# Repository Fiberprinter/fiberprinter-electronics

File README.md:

<div align="center">
<h1 align="center">

<br>Fiberelectronics
</h1>
<h3>Control every pulse, master every micron</h3>

</div>

</h1>

# Fiberprinter Electronics

Dieses Repository enthält die Elektronikentwicklung für den faserverlegenden 3D-Drucker, der im Rahmen einer Diplomarbeit an der HTBLA Kaindorf entwickelt wird. Die Elektronik umfasst sowohl die Steuerung der Druckkopffunktionen als auch die Anbindung an das Hauptsystem mittels eines Raspberry Pi mit **Klipper-Firmware**.

## 📌 Projektübersicht

Das Ziel dieses Projekts ist die Entwicklung einer modularen und effizienten Steuerung für den Druckkopf, die über eine eigenentwickelte Platine mit einem **ATmega328** realisiert wird. Diese übernimmt spezifische Aufgaben, die über das Hauptsystem des Druckers nicht direkt gesteuert werden.

## ⚙️ Hauptkomponenten

### 1️⃣ **Steuerungshardware**
- **Raspberry Pi** mit Klipper-Firmware zur übergeordneten Steuerung
- **Eigenes Mainboard mit ATmega328** zur Ansteuerung folgender Komponenten:
  - Lüfter
  - BL Touch (Autoleveling-Sensor)
  - Servo
  - Schrittmotor
  - Temperatursensoren
- **Breakout-Board für den ATmega2560**, das Test- und Messpunkte sowie einen Bootloader enthält
- **FT232RL** als USB-to-Serial-Adapter für die Kommunikation mit dem ATmega2560
- **Reset-Button** zur einfachen Rücksetzung des Systems

### 2️⃣ **Firmware & Kommunikation**
- Der **ATmega328** wird von der Klipper-Firmware auf dem Raspberry Pi über USB angesprochen
- Kommunikation erfolgt über **serielles Protokoll**
- Entwicklung einer **angepassten Firmware für den ATmega328**, um die spezifischen Druckkopf-Funktionen auszuführen

### 3️⃣ **Software**
- Python-Skript zur **Integration der Steuerung in Klipper**
- Implementierung eines Protokolls zur **Steuerung der Hardware aus Klipper heraus**
- Zusammenarbeit mit der **Slicing-Software**, um die gezielte Faserverlegung zu ermöglichen

## 🛠️ Entwicklungsteam

- **Jan Traußnigg** – Elektronikdesign & Firmware
- **Nico Hütter** – Konstruktion, Aufbau & Testung
- **Elias Gottsbacher** – Slicing-Software & Software-Integration

## 📜 Lizenz

Dieses Projekt steht unter der **MIT-Lizenz**. Weitere Details sind in der Datei `LICENSE` zu finden.

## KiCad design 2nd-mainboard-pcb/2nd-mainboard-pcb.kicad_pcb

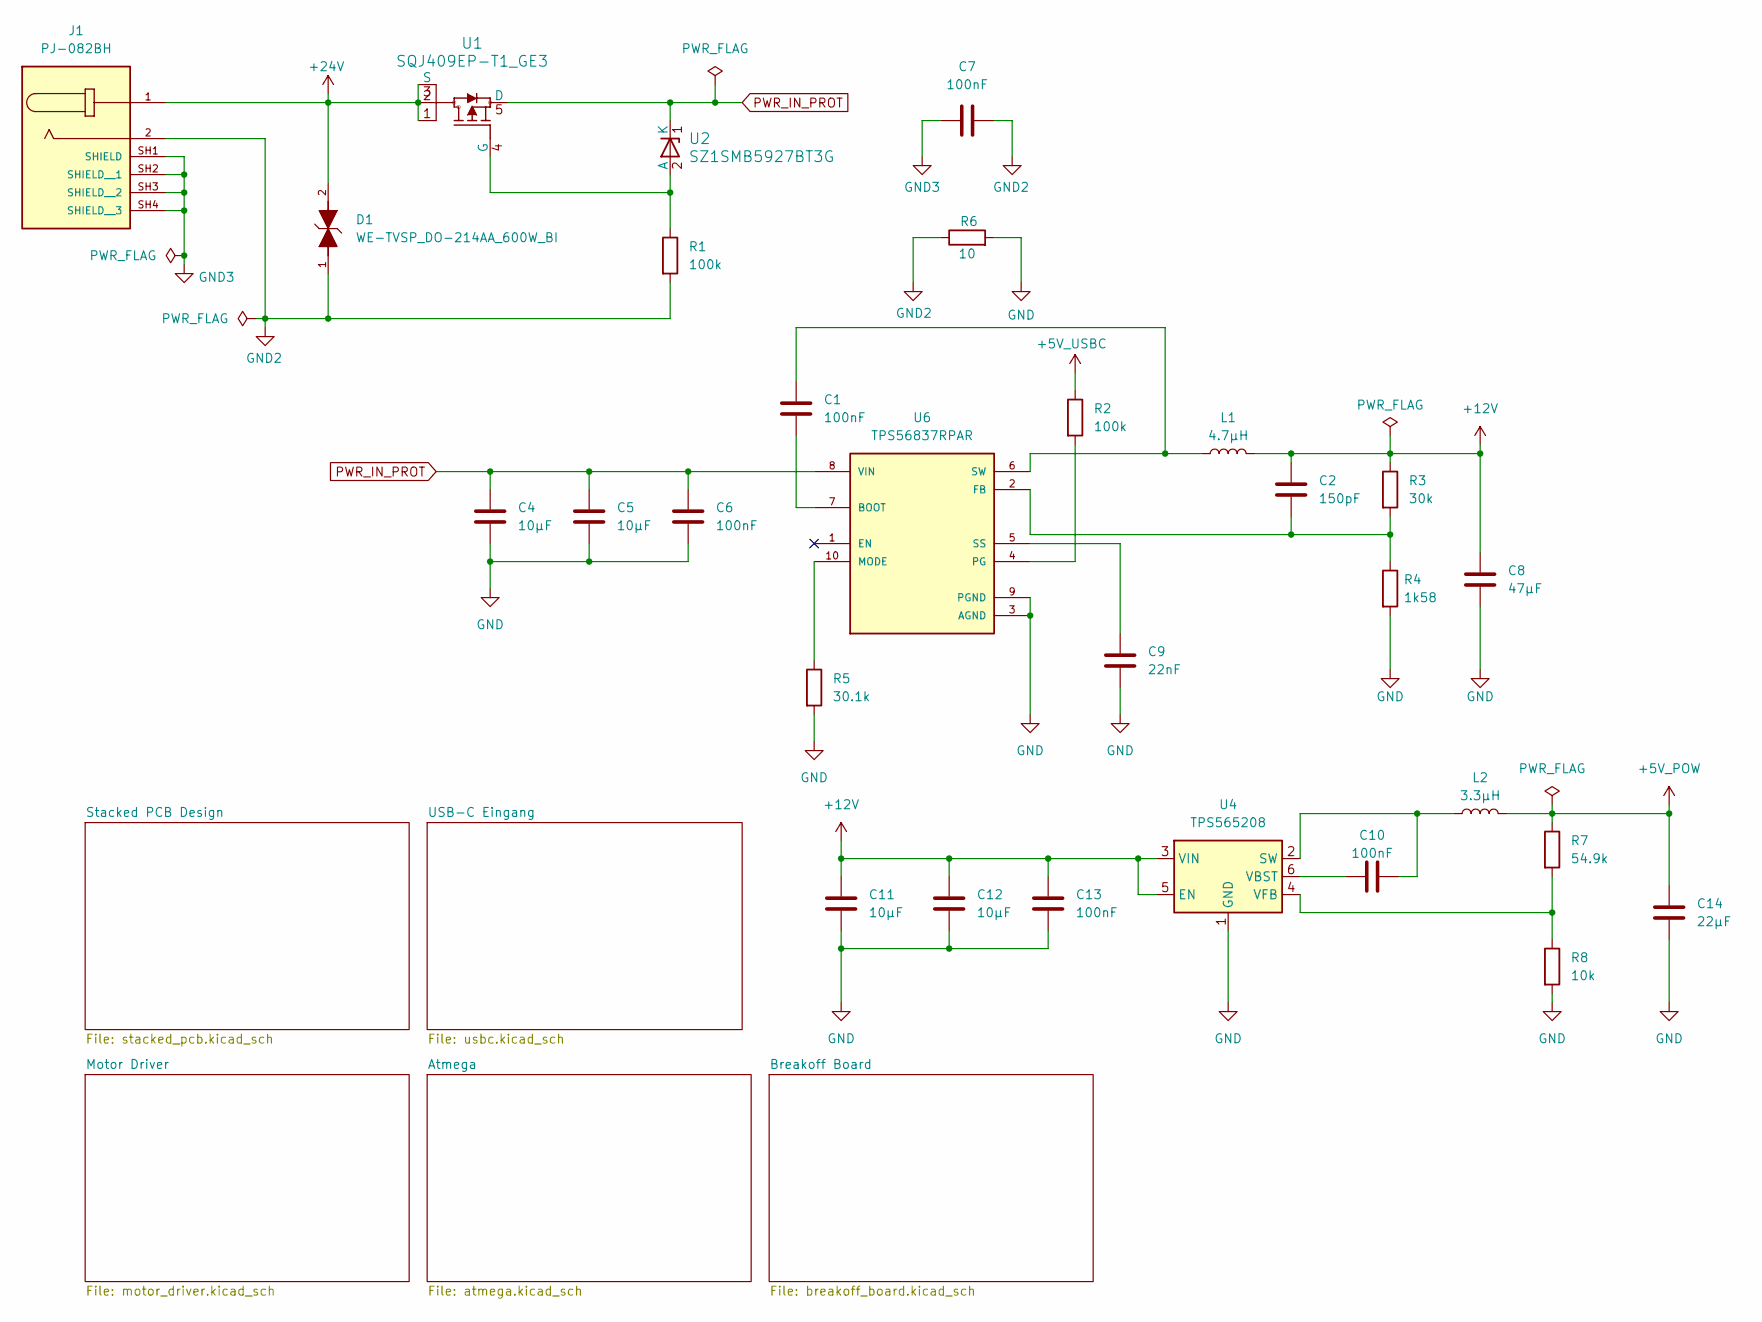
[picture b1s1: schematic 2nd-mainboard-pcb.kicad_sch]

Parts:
C1, C7, C10, C13: 100nF; C_0603_1608Metric_Pad1.08x0.95mm_HandSolder
C2: 150pF; C_0603_1608Metric_Pad1.08x0.95mm_HandSolder
C4, C5: 10µF; C_1210_3225Metric_Pad1.33x2.70mm_HandSolder
C6: 100nF; C_0805_2012Metric_Pad1.18x1.45mm_HandSolder
C8: 47µF; C_1812_4532Metric_Pad1.57x3.40mm_HandSolder
C9: 22nF; C_0603_1608Metric_Pad1.08x0.95mm_HandSolder
C11, C12: 10µF; C_0805_2012Metric_Pad1.18x1.45mm_HandSolder
C14: 22µF; C_1210_3225Metric_Pad1.33x2.70mm_HandSolder
D1: WE-TVSP_DO-214AA_600W_BI; 824521241
J1: PJ-082BH; CUI_PJ-082BH; PARTREV 1.04
L1: 4.7µH; SPM10040T_4R7M_HZ
L2: 3.3µH; IHLP2525CZER3R3M11
R1, R2: 100k; R_0603_1608Metric_Pad0.98x0.95mm_HandSolder
R3: 30k; R_0603_1608Metric_Pad0.98x0.95mm_HandSolder
R4: 1k58; R_0603_1608Metric_Pad0.98x0.95mm_HandSolder
R5: 30.1k; R_0603_1608Metric_Pad0.98x0.95mm_HandSolder
R6: 10; R_0603_1608Metric_Pad0.98x0.95mm_HandSolder
R7: 54.9k; R_0603_1608Metric_Pad0.98x0.95mm_HandSolder
R8: 10k; R_0603_1608Metric_Pad0.98x0.95mm_HandSolder
U1: SQJ409EP-T1_GE3; SQJ409EP_T1_GE3
U2: SZ1SMB5927BT3G
U4: TPS565208; SOT-23-6
U6: TPS56837RPAR; CONV_TPS56837RPAR; PARTREV A

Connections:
+5V_POW: C14.1, L2.2, R7.1; also elsewhere on the board
+12V: C2.1, C8.1, C11.1, C12.1, C13.1, L1.2, R3.1, U4.3 (VIN), U4.5 (EN); also elsewhere on the board
+24V: D1.2, J1.1, U1.1, U1.2, U1.3 (S)
AREF: R2.1; also elsewhere on the board
GND: C4.2, C5.2, C6.2, C8.2, C9.2, C11.2, C12.2, C13.2, C14.2, R4.2, R5.2, R6.2, R8.2, U4.1 (GND), U6.3 (AGND), U6.9 (PGND); also elsewhere on the board
GND2: C7.2, D1.1, J1.2, R1.2, R6.1
GND3: C7.1, J1.SH1 (SHIELD), J1.SH2 (SHIELD__1), J1.SH3 (SHIELD__2), J1.SH4 (SHIELD__3)
unnamed: R1.1, U1.4 (G), U2.2 (A)
unnamed: C10.2, L2.1, U4.2 (SW)
unnamed: C10.1, U4.6 (VBST)
unnamed: R7.2, R8.1, U4.4 (VFB)
unnamed: C1.1, U6.7 (BOOT)
unnamed: C2.2, R3.2, R4.1, U6.2 (FB)
unnamed: R5.1, U6.10 (MODE)
unnamed: R2.2, U6.4 (PG)
unnamed: C9.1, U6.5 (SS)
unnamed: C1.2, L1.1, U6.6 (SW)
PWR_IN_PROT: C4.1, C5.1, C6.1, U1.5 (D), U2.1 (K), U6.8 (VIN)

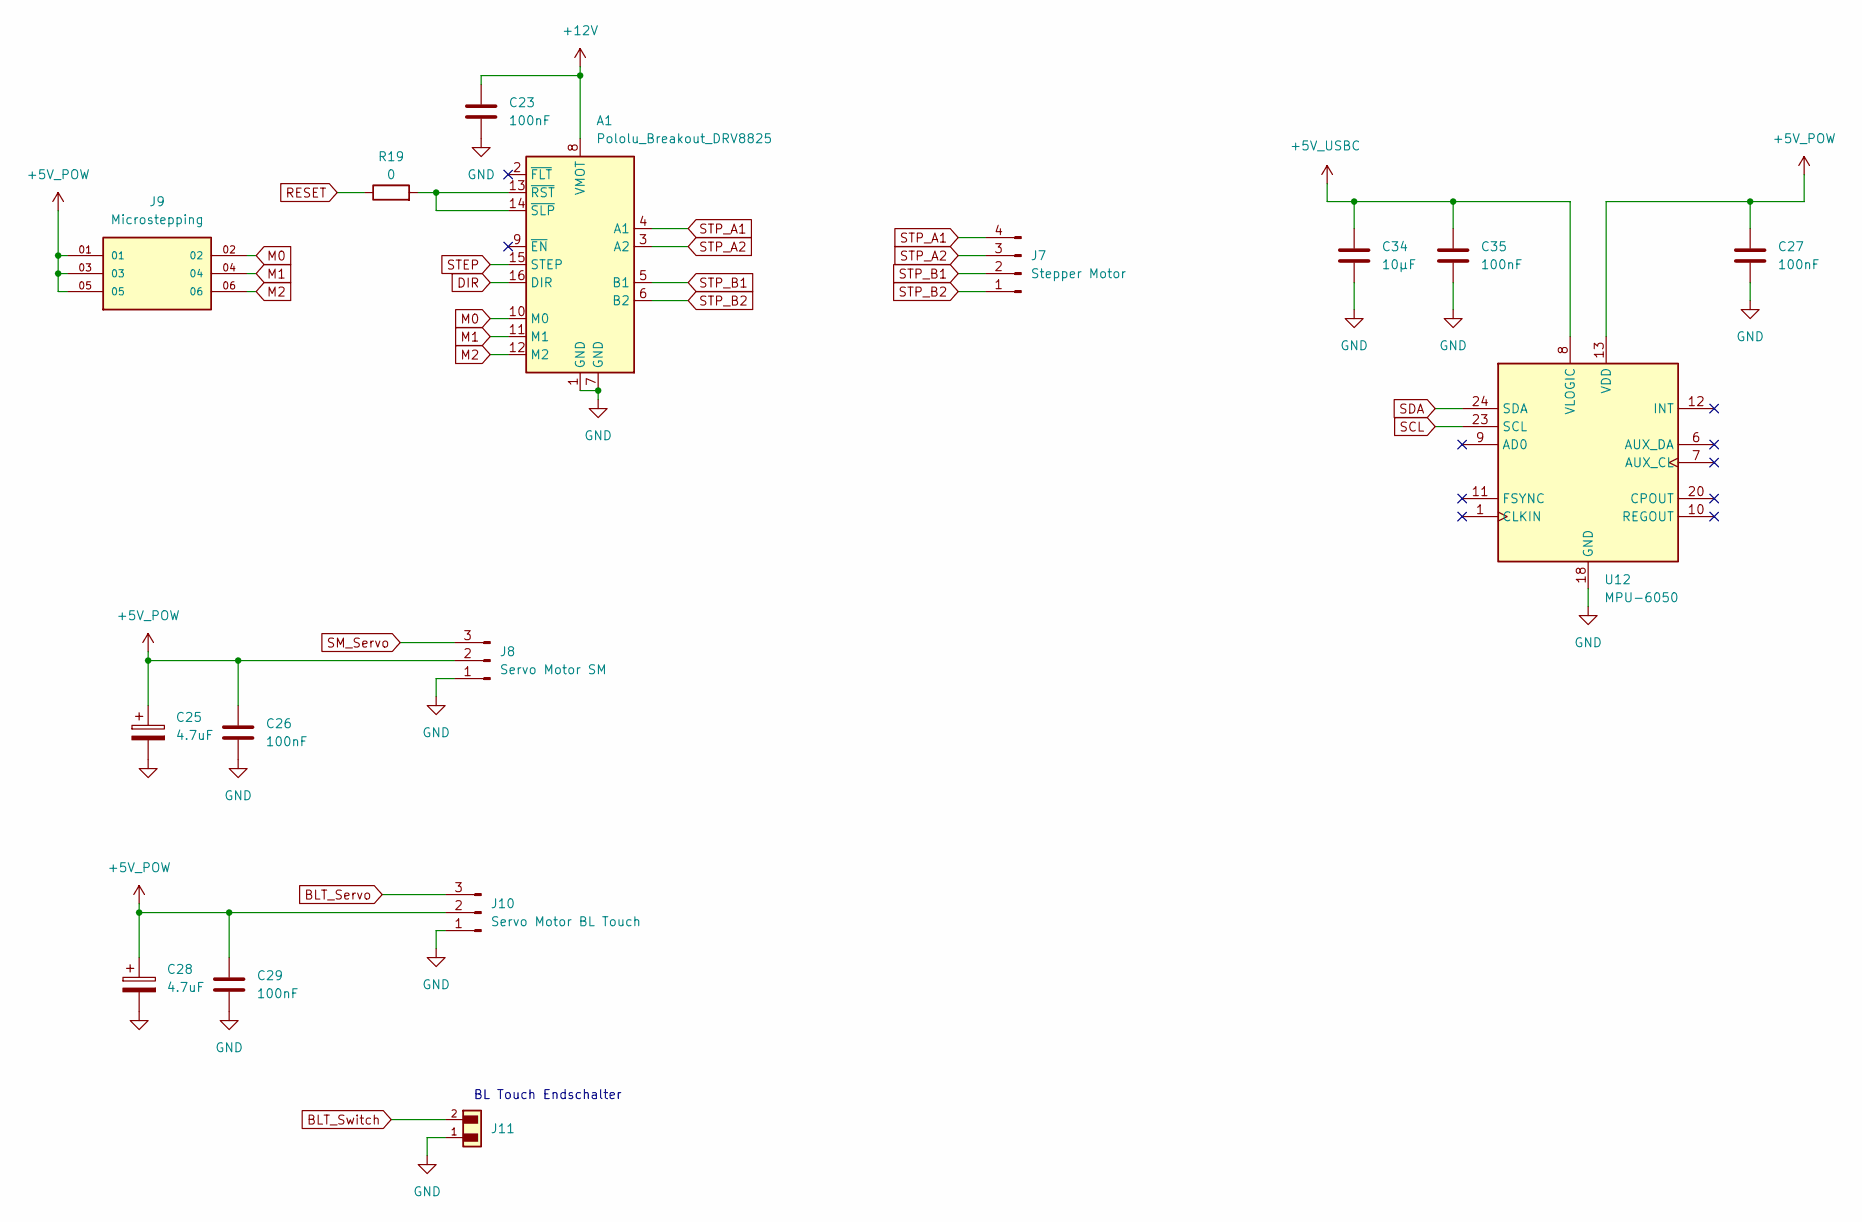
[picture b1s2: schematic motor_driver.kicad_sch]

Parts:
A1: Pololu_Breakout_DRV8825; drv8825
C23, C26, C27, C29, C35: 100nF; C_0603_1608Metric_Pad1.08x0.95mm_HandSolder
C25, C28: 4.7uF; C_0805_2012Metric_Pad1.18x1.45mm_HandSolder
C34: 10µF; C_0805_2012Metric_Pad1.18x1.45mm_HandSolder
J7: Stepper Motor; JST_S4B-XH-A-1
J8: Servo Motor SM; JST_XH_S3B-XH-A_1x03_P2.50mm_Horizontal
J9: Microstepping; FTSH-103-01-L-DH; PARTREV R
J10: Servo Motor BL Touch; JST_XH_S3B-XH-A_1x03_P2.50mm_Horizontal
J11: T3; 665102131822; PART-NUMBER 665102131822
R19: 0; R_0603_1608Metric_Pad0.98x0.95mm_HandSolder
U12: MPU-6050; InvenSense_QFN-24_4x4mm_P0.5mm

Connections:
+5V_POW: C25.1, C26.1, C27.1, C28.1, C29.1, J8.2, J9.01, J9.03, J9.05, J10.2, U12.13 (VDD); also elsewhere on the board
+12V: A1.8 (VMOT), C23.1; also elsewhere on the board
AREF: C34.1, C35.1, U12.8 (VLOGIC); also elsewhere on the board
BLT_Servo: J10.3; also elsewhere on the board
BLT_Switch: J11.2; also elsewhere on the board
DIR: A1.16 (DIR); also elsewhere on the board
GND: A1.1 (GND), A1.7 (GND), C23.2, C25.2, C26.2, C27.2, C28.2, C29.2, C34.2, C35.2, J8.1, J10.1, J11.1, U12.18 (GND); also elsewhere on the board
M0: A1.10 (M0), J9.02
M1: A1.11 (M1), J9.04
M2: A1.12 (M2), J9.06
MOSI: J8.3; also elsewhere on the board
unnamed: A1.13 (~RST), A1.14 (~SLP), R19.2
RESET: R19.1; also elsewhere on the board
SCL: U12.23 (SCL); also elsewhere on the board
SDA: U12.24 (SDA); also elsewhere on the board
STEP: A1.15 (STEP); also elsewhere on the board
STP_A1: A1.4 (A1), J7.4
STP_A2: A1.3 (A2), J7.3
STP_B1: A1.5 (B1), J7.2
STP_B2: A1.6 (B2), J7.1

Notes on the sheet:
BL Touch Endschalter

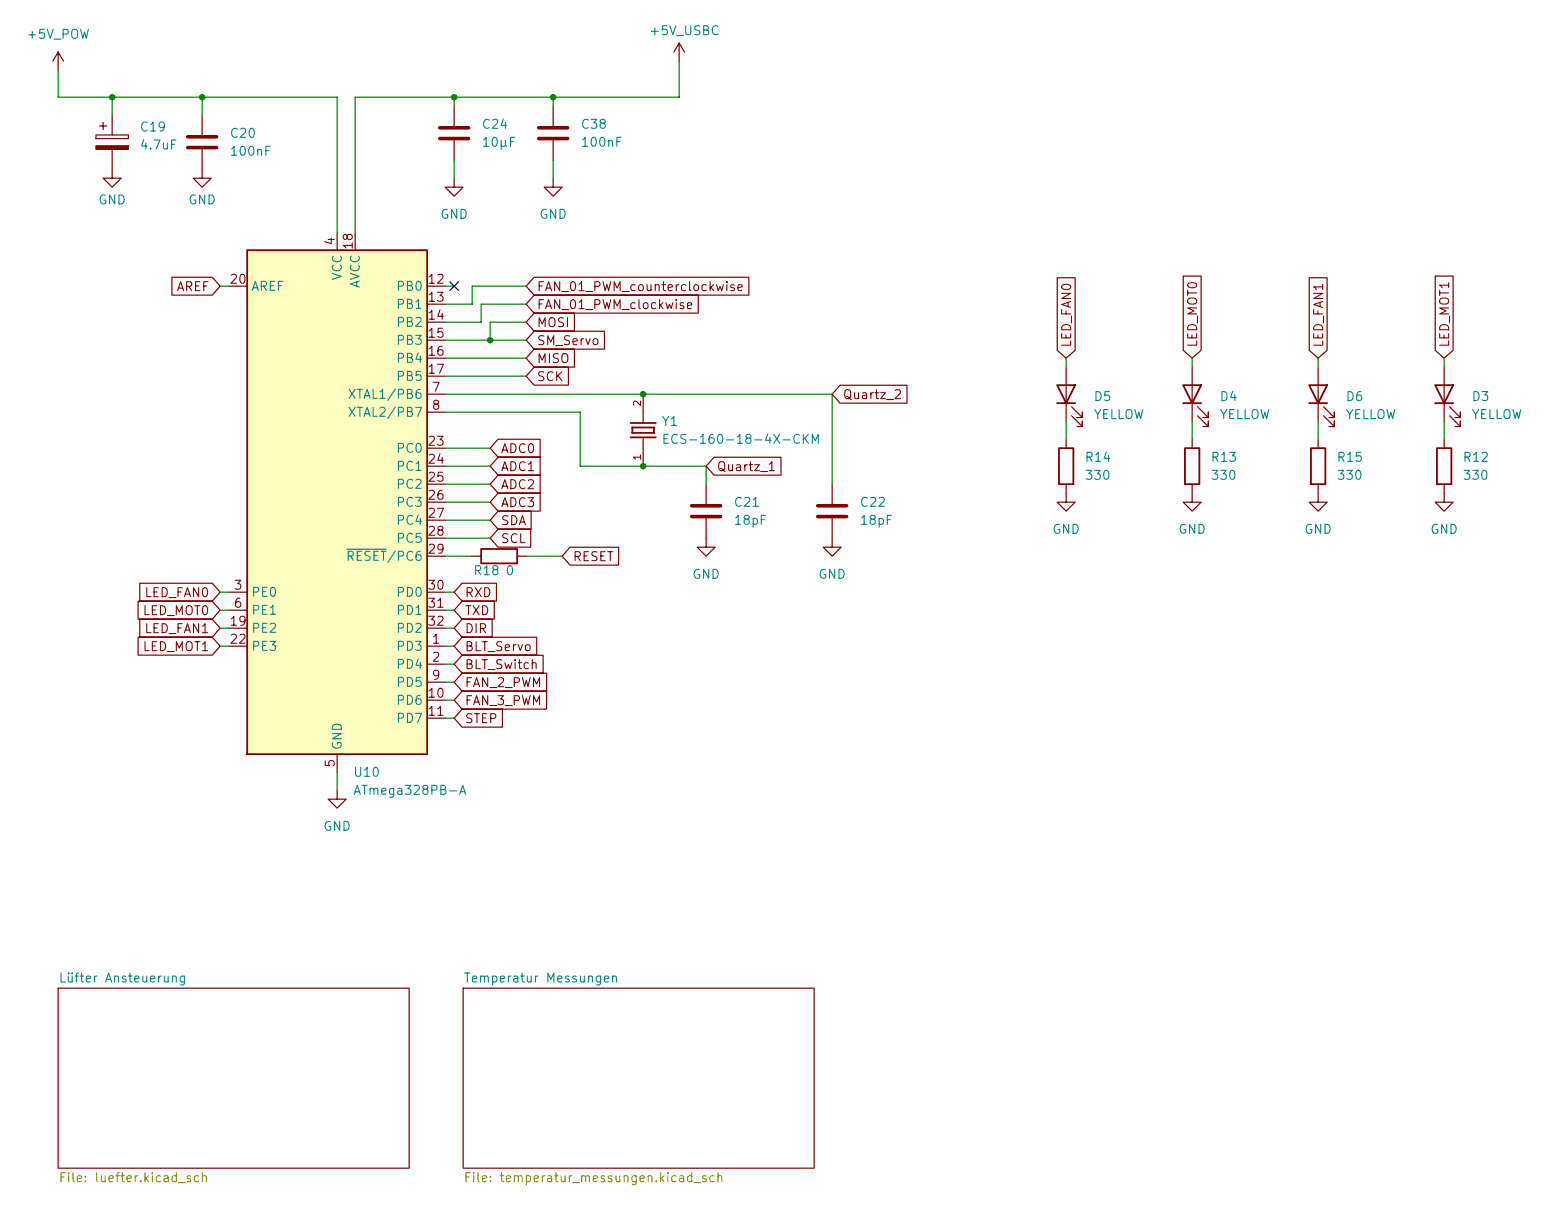
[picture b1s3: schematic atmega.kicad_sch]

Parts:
C19: 4.7uF; C_0805_2012Metric_Pad1.18x1.45mm_HandSolder
C20, C38: 100nF; C_0603_1608Metric_Pad1.08x0.95mm_HandSolder
C21, C22: 18pF; C_0603_1608Metric_Pad1.08x0.95mm_HandSolder
C24: 10µF; C_0805_2012Metric_Pad1.18x1.45mm_HandSolder
D3, D4, D5, D6: YELLOW; LED_0805_2012Metric
R12, R13, R14, R15: 330; R_0603_1608Metric_Pad0.98x0.95mm_HandSolder
R18: 0; R_0603_1608Metric_Pad0.98x0.95mm_HandSolder
U10: ATmega328PB-A; TQFP-32_7x7mm_P0.8mm
Y1: ECS-160-18-4X-CKM; XTAL_ECS-160-18-4X-CKM

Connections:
+5V_POW: C19.1, C20.1, U10.4 (VCC); also elsewhere on the board
ADC0: U10.23 (PC0); also elsewhere on the board
ADC1: U10.24 (PC1); also elsewhere on the board
ADC2: U10.25 (PC2); also elsewhere on the board
ADC3: U10.26 (PC3); also elsewhere on the board
AREF: C24.1, C38.1, U10.18 (AVCC), U10.20 (AREF); also elsewhere on the board
BLT_Servo: U10.1 (PD3); also elsewhere on the board
BLT_Switch: U10.2 (PD4); also elsewhere on the board
DIR: U10.32 (PD2); also elsewhere on the board
FAN_01_PWM_clockwise: U10.14 (PB2); also elsewhere on the board
FAN_01_PWM_counterclockwise: U10.13 (PB1); also elsewhere on the board
FAN_2_PWM: U10.9 (PD5); also elsewhere on the board
FAN_3_PWM: U10.10 (PD6); also elsewhere on the board
GND: C19.2, C20.2, C21.2, C22.2, C24.2, C38.2, R12.2, R13.2, R14.2, R15.2, U10.5 (GND), U10.21 (GND); also elsewhere on the board
LED_FAN0: D5.2 (A), U10.3 (PE0); also elsewhere on the board
LED_FAN1: D6.2 (A), U10.19 (PE2); also elsewhere on the board
LED_MOT0: D4.2 (A), U10.6 (PE1); also elsewhere on the board
LED_MOT1: D3.2 (A), U10.22 (PE3); also elsewhere on the board
MISO: U10.16 (PB4); also elsewhere on the board
MOSI: U10.15 (PB3); also elsewhere on the board
unnamed: D3.1 (K), R12.1
unnamed: D4.1 (K), R13.1
unnamed: D5.1 (K), R14.1
unnamed: D6.1 (K), R15.1
unnamed: R18.1, U10.29 (~RESET/PC6)
Quartz_1: C21.1, U10.8 (XTAL2/PB7), Y1.1; also elsewhere on the board
Quartz_2: C22.1, U10.7 (XTAL1/PB6), Y1.2; also elsewhere on the board
RESET: R18.2; also elsewhere on the board
RXD: U10.30 (PD0); also elsewhere on the board
SCK: U10.17 (PB5); also elsewhere on the board
SCL: U10.28 (PC5); also elsewhere on the board
SDA: U10.27 (PC4); also elsewhere on the board
STEP: U10.11 (PD7); also elsewhere on the board
TXD: U10.31 (PD1); also elsewhere on the board

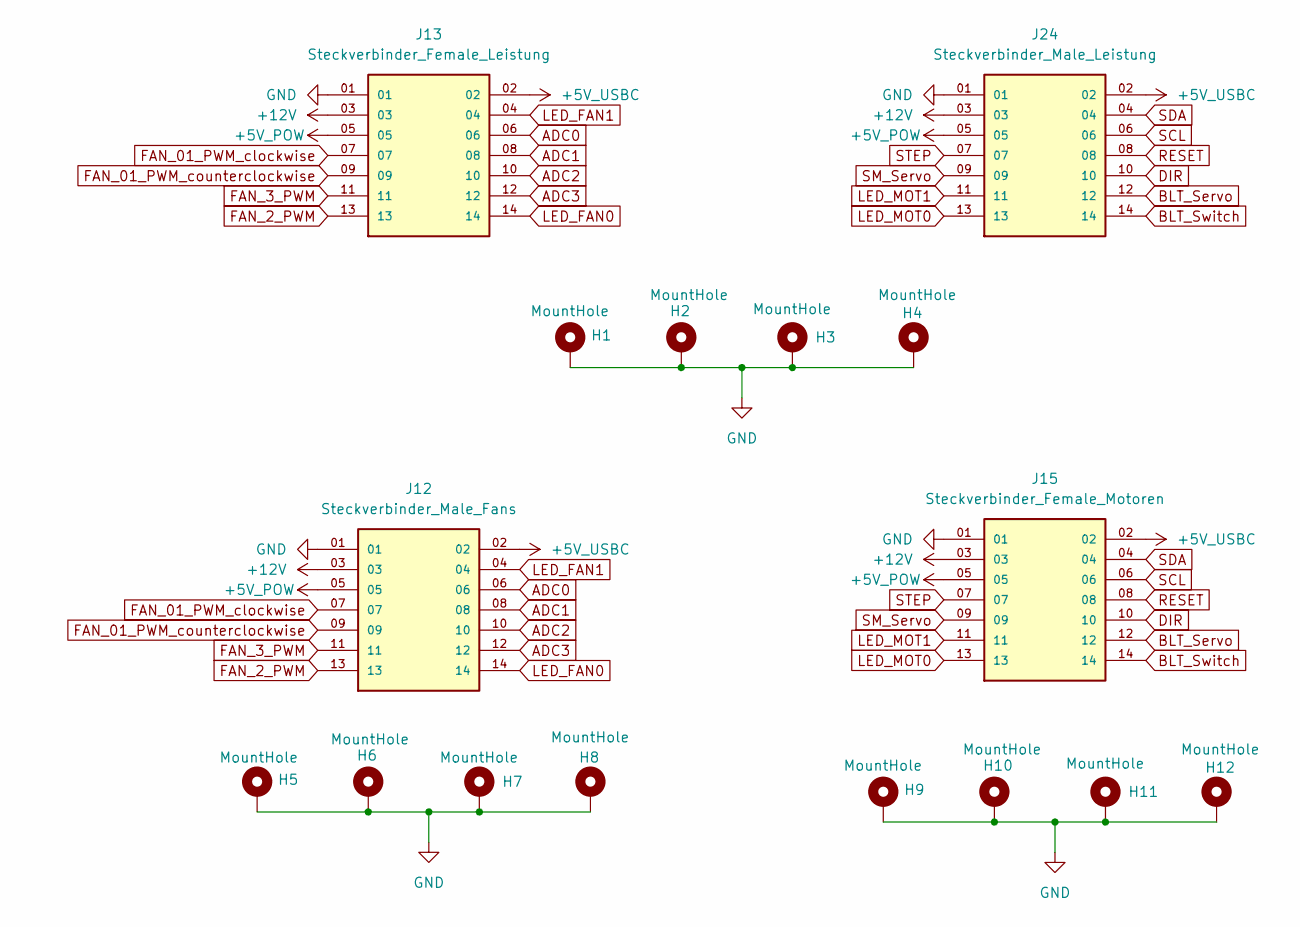
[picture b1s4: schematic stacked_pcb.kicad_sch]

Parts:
H1, H2, H3, H4: MountHole; MountingHole_2.7mm_M2.5_ISO7380_Pad_TopBottom_7mm
H5, H6, H7, H8: MountHole; MountingHole_2.7mm_M2.5_ISO7380_Pad_TopBottom_111mm
H9, H10, H11, H12: MountHole; MountingHole_2.7mm_M2.5_ISO7380_Pad_TopBottom
J12: Steckverbinder_Male_Fans; SAMTEC_TSM-107-04-L-DV
J13: Steckverbinder_Female_Leistung; SAMTEC_HLE-107-02-L-DV; PARTREV R
J15: Steckverbinder_Female_Motoren; SAMTEC_HLE-107-02-L-DV; PARTREV R
J24: Steckverbinder_Male_Leistung; SAMTEC_HW-07-08-L-D-250-SM; PARTREV R

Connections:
+5V_POW: J12.05, J13.05, J15.05, J24.05; also elsewhere on the board
+12V: J12.03, J13.03, J15.03, J24.03; also elsewhere on the board
ADC0: J12.06, J13.06; also elsewhere on the board
ADC1: J12.08, J13.08; also elsewhere on the board
ADC2: J12.10, J13.10; also elsewhere on the board
ADC3: J12.12, J13.12; also elsewhere on the board
AREF: J12.02, J13.02, J15.02, J24.02; also elsewhere on the board
BLT_Servo: J15.12, J24.12; also elsewhere on the board
BLT_Switch: J15.14, J24.14; also elsewhere on the board
DIR: J15.10, J24.10; also elsewhere on the board
FAN_01_PWM_clockwise: J12.07, J13.07; also elsewhere on the board
FAN_01_PWM_counterclockwise: J12.09, J13.09; also elsewhere on the board
FAN_2_PWM: J12.13, J13.13; also elsewhere on the board
FAN_3_PWM: J12.11, J13.11; also elsewhere on the board
GND: H1.1, H2.1, H3.1, H4.1, H5.1, H6.1, H7.1, H8.1, H9.1, H10.1, H11.1, H12.1, J12.01, J13.01, J15.01, J24.01; also elsewhere on the board
LED_FAN0: J12.14, J13.14; also elsewhere on the board
LED_FAN1: J12.04, J13.04; also elsewhere on the board
LED_MOT0: J15.13, J24.13; also elsewhere on the board
LED_MOT1: J15.11, J24.11; also elsewhere on the board
MOSI: J15.09, J24.09; also elsewhere on the board
RESET: J15.08, J24.08; also elsewhere on the board
SCL: J15.06, J24.06; also elsewhere on the board
SDA: J15.04, J24.04; also elsewhere on the board
STEP: J15.07, J24.07; also elsewhere on the board

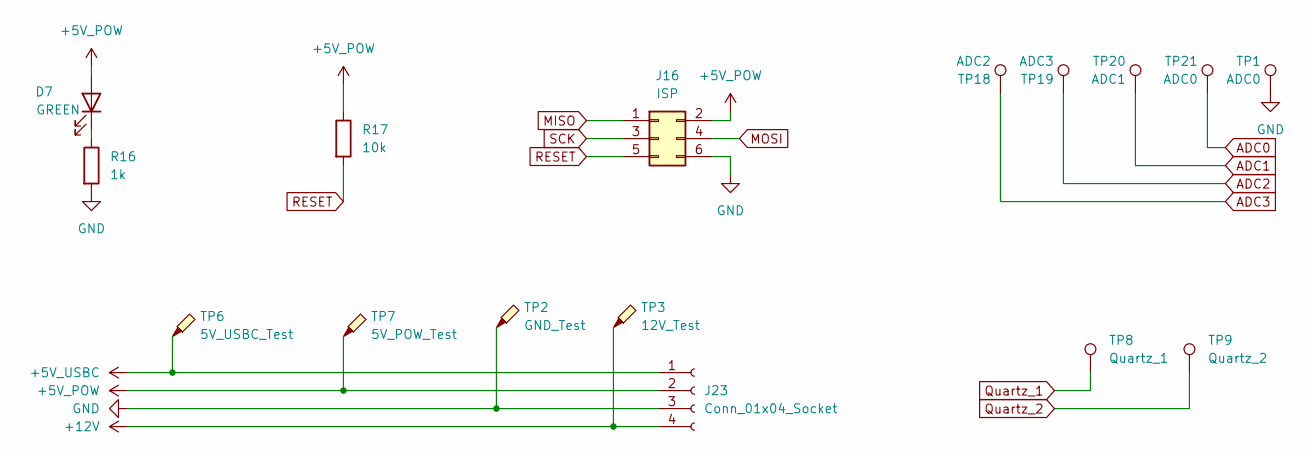
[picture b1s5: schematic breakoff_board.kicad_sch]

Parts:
D7: GREEN; LED_0805_2012Metric
J16: ISP; PinHeader_2x03_P2.54mm_Vertical
J23: Conn_01x04_Socket; PinSocket_1x04_P2.54mm_Vertical
R16: 1k; R_0603_1608Metric_Pad0.98x0.95mm_HandSolder
R17: 10k; R_0603_1608Metric_Pad0.98x0.95mm_HandSolder
TP1, TP21: ADC0; TestPoint_Pad_D2.0mm
TP2: GND_Test; TestPoint_Pad_D3.0mm
TP3: 12V_Test; TestPoint_Pad_D3.0mm
TP6: 5V_USBC_Test; TestPoint_Pad_D3.0mm
TP7: 5V_POW_Test; TestPoint_Pad_D3.0mm
TP8: Quartz_1; TestPoint_Loop_D3.80mm_Drill2.5mm
TP9: Quartz_2; TestPoint_Loop_D3.80mm_Drill2.5mm
TP18: ADC2; TestPoint_Pad_D2.0mm
TP19: ADC3; TestPoint_Pad_D2.0mm
TP20: ADC1; TestPoint_Pad_D2.0mm

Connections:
+5V_POW: D7.2 (A), J16.2, J23.2, R17.1, TP7.1; also elsewhere on the board
+12V: J23.4, TP3.1; also elsewhere on the board
ADC0: TP21.1; also elsewhere on the board
ADC1: TP20.1; also elsewhere on the board
ADC2: TP19.1; also elsewhere on the board
ADC3: TP18.1; also elsewhere on the board
AREF: J23.1, TP6.1; also elsewhere on the board
GND: J16.6, J23.3, R16.2, TP1.1, TP2.1; also elsewhere on the board
MISO: J16.1; also elsewhere on the board
MOSI: J16.4; also elsewhere on the board
unnamed: D7.1 (K), R16.1
Quartz_1: TP8.1; also elsewhere on the board
Quartz_2: TP9.1; also elsewhere on the board
RESET: J16.5, R17.2; also elsewhere on the board
SCK: J16.3; also elsewhere on the board

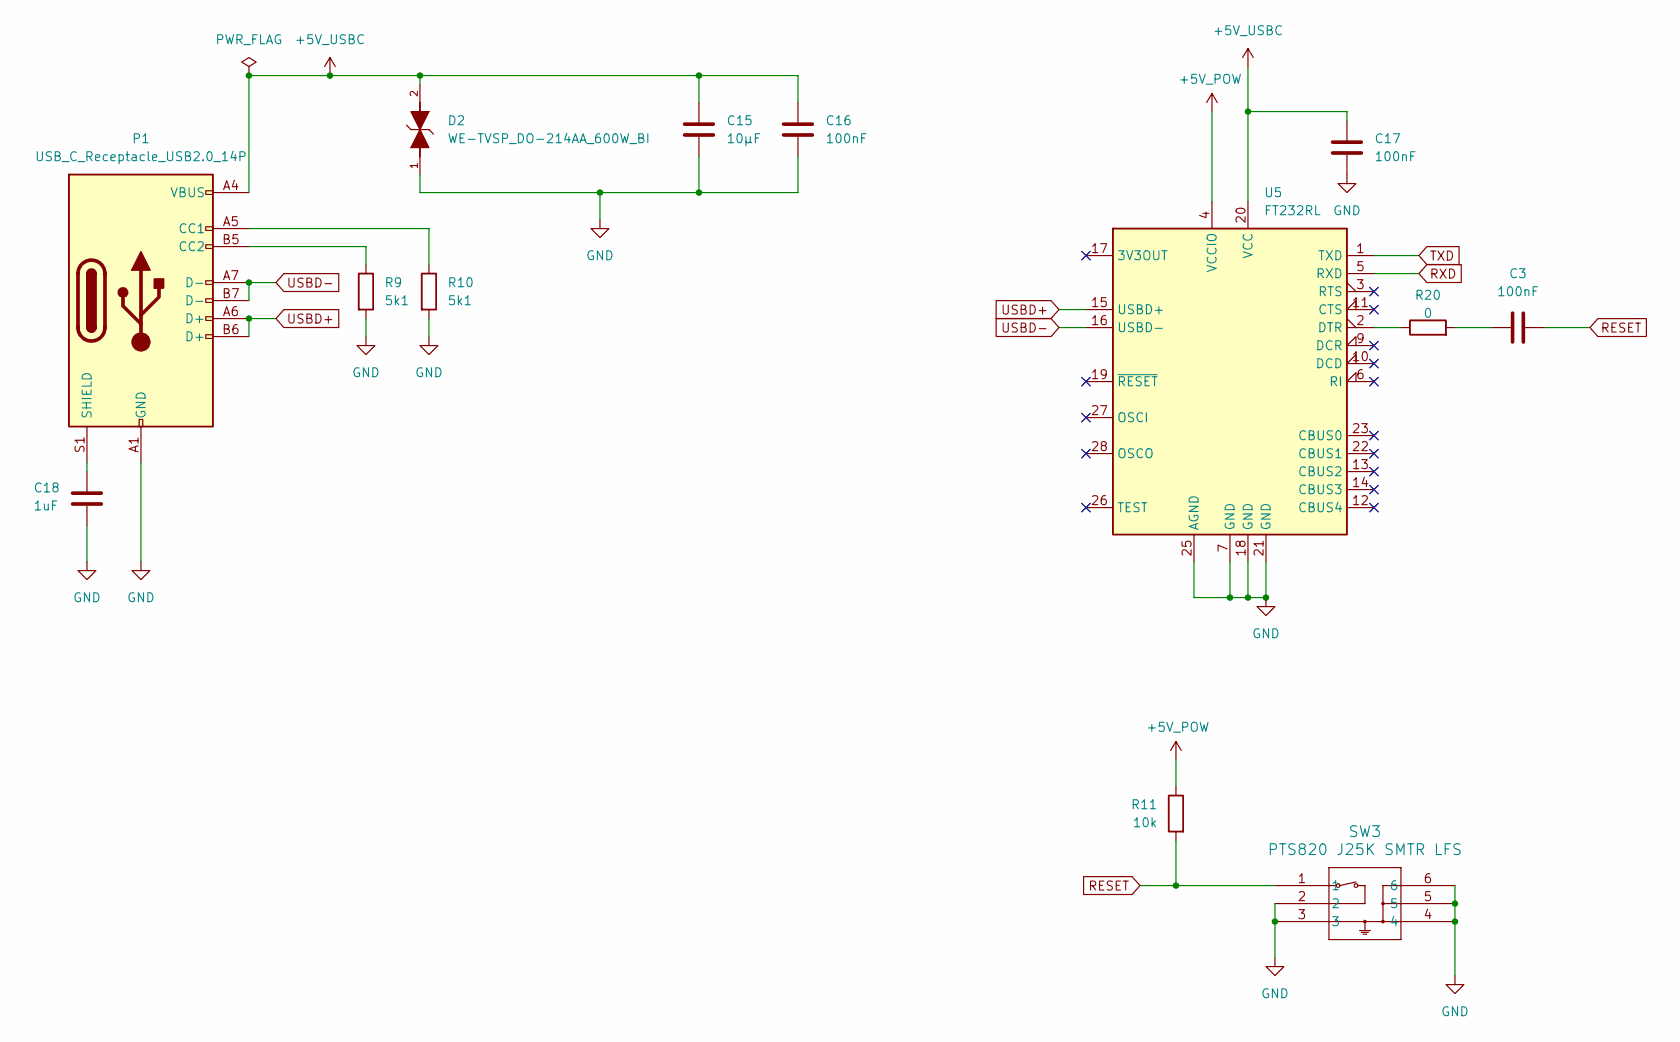
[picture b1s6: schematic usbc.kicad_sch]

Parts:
C3, C16, C17: 100nF; C_0603_1608Metric_Pad1.08x0.95mm_HandSolder
C15: 10µF; C_0805_2012Metric_Pad1.18x1.45mm_HandSolder
C18: 1uF; C_0805_2012Metric_Pad1.18x1.45mm_HandSolder
D2: WE-TVSP_DO-214AA_600W_BI; 824521241
P1: USB_C_Receptacle_USB2.0_14P; USB_C_Receptacle_GCT_USB4085
R9, R10: 5k1; R_0603_1608Metric_Pad0.98x0.95mm_HandSolder
R11: 10k; R_0603_1608Metric_Pad0.98x0.95mm_HandSolder
R20: 0; R_0603_1608Metric_Pad0.98x0.95mm_HandSolder
SW3: PTS820 J25K SMTR LFS; PTS820 J25K SMTR LFS_CNK
U5: FT232RL; SSOP-28_5.3x10.2mm_P0.65mm

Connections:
+5V_POW: R11.1, U5.4 (VCCIO); also elsewhere on the board
AREF: C15.1, C16.1, C17.1, D2.2, P1.A4 (VBUS), P1.A9 (VBUS), P1.B4 (VBUS), P1.B9 (VBUS), U5.20 (VCC); also elsewhere on the board
GND: C15.2, C16.2, C17.2, C18.2, D2.1, P1.A1 (GND), P1.A12 (GND), P1.B1 (GND), P1.B12 (GND), R9.2, R10.2, SW3.2, SW3.3, SW3.4, SW3.5, SW3.6, U5.7 (GND), U5.18 (GND), U5.21 (GND), U5.25 (AGND); also elsewhere on the board
unnamed: C3.1, R20.2
unnamed: P1.A5 (CC1), R10.1
unnamed: P1.B5 (CC2), R9.1
unnamed: C18.1, P1.S1 (SHIELD)
unnamed: R20.1, U5.2 (DTR)
RESET: C3.2, R11.2, SW3.1; also elsewhere on the board
RXD: U5.5 (RXD); also elsewhere on the board
TXD: U5.1 (TXD); also elsewhere on the board
USBD+: P1.A6 (D+), P1.B6 (D+), U5.15 (USBD+)
USBD-: P1.A7 (D-), P1.B7 (D-), U5.16 (USBD-)

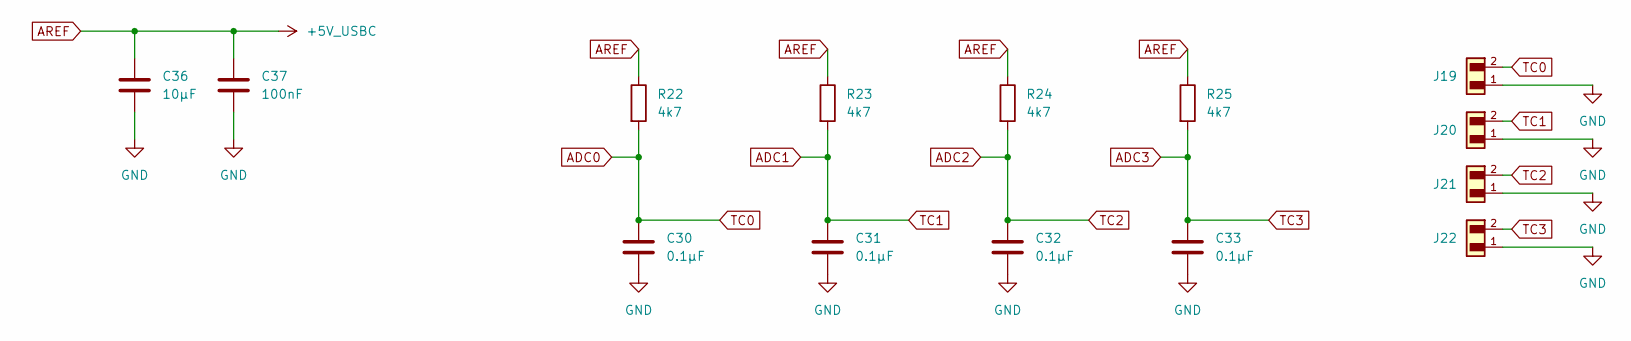
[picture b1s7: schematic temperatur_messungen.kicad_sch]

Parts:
C30, C31, C32, C33: 0.1µF; C_0603_1608Metric_Pad1.08x0.95mm_HandSolder
C36: 10µF; C_0805_2012Metric_Pad1.18x1.45mm_HandSolder
C37: 100nF; C_0603_1608Metric_Pad1.08x0.95mm_HandSolder
J19, J20, J21: T2; 665102131822; PART-NUMBER 665102131822
J22: T3; 665102131822; PART-NUMBER 665102131822
R22, R23, R24, R25: 4k7; R_0603_1608Metric_Pad0.98x0.95mm_HandSolder

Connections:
ADC0: C30.1, J19.2, R22.2; also elsewhere on the board
ADC1: C31.1, J20.2, R23.2; also elsewhere on the board
ADC2: C32.1, J21.2, R24.2; also elsewhere on the board
ADC3: C33.1, J22.2, R25.2; also elsewhere on the board
AREF: C36.1, C37.1, R22.1, R23.1, R24.1, R25.1; also elsewhere on the board
GND: C30.2, C31.2, C32.2, C33.2, C36.2, C37.2, J19.1, J20.1, J21.1, J22.1; also elsewhere on the board

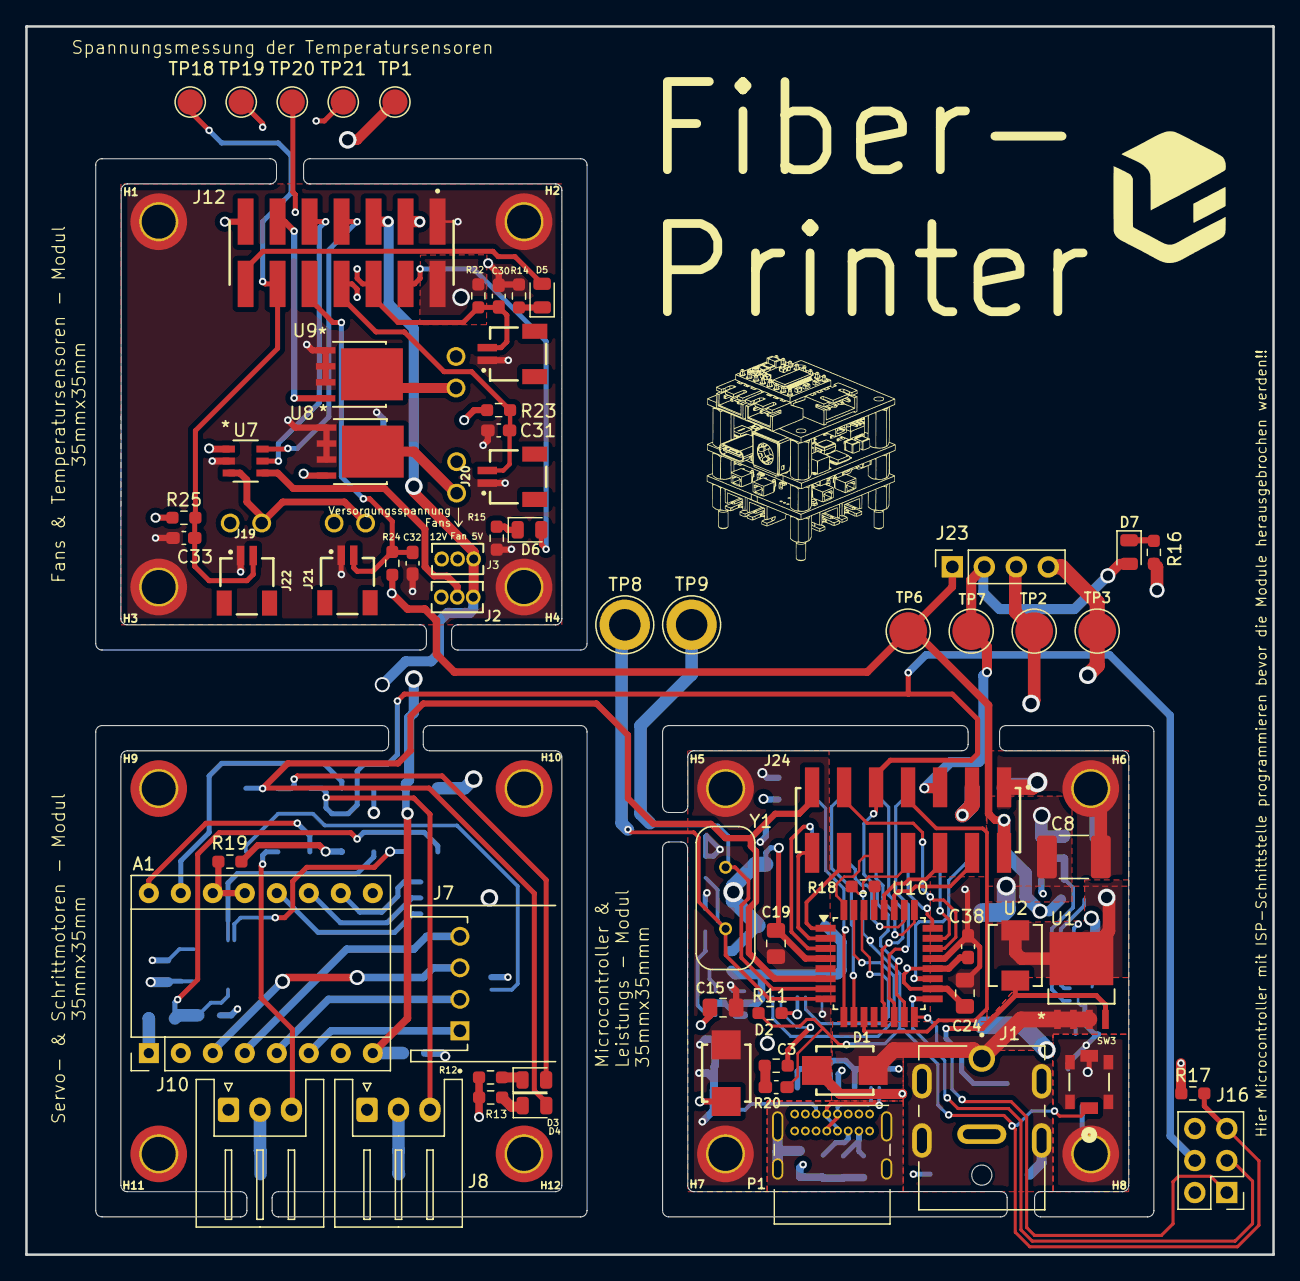
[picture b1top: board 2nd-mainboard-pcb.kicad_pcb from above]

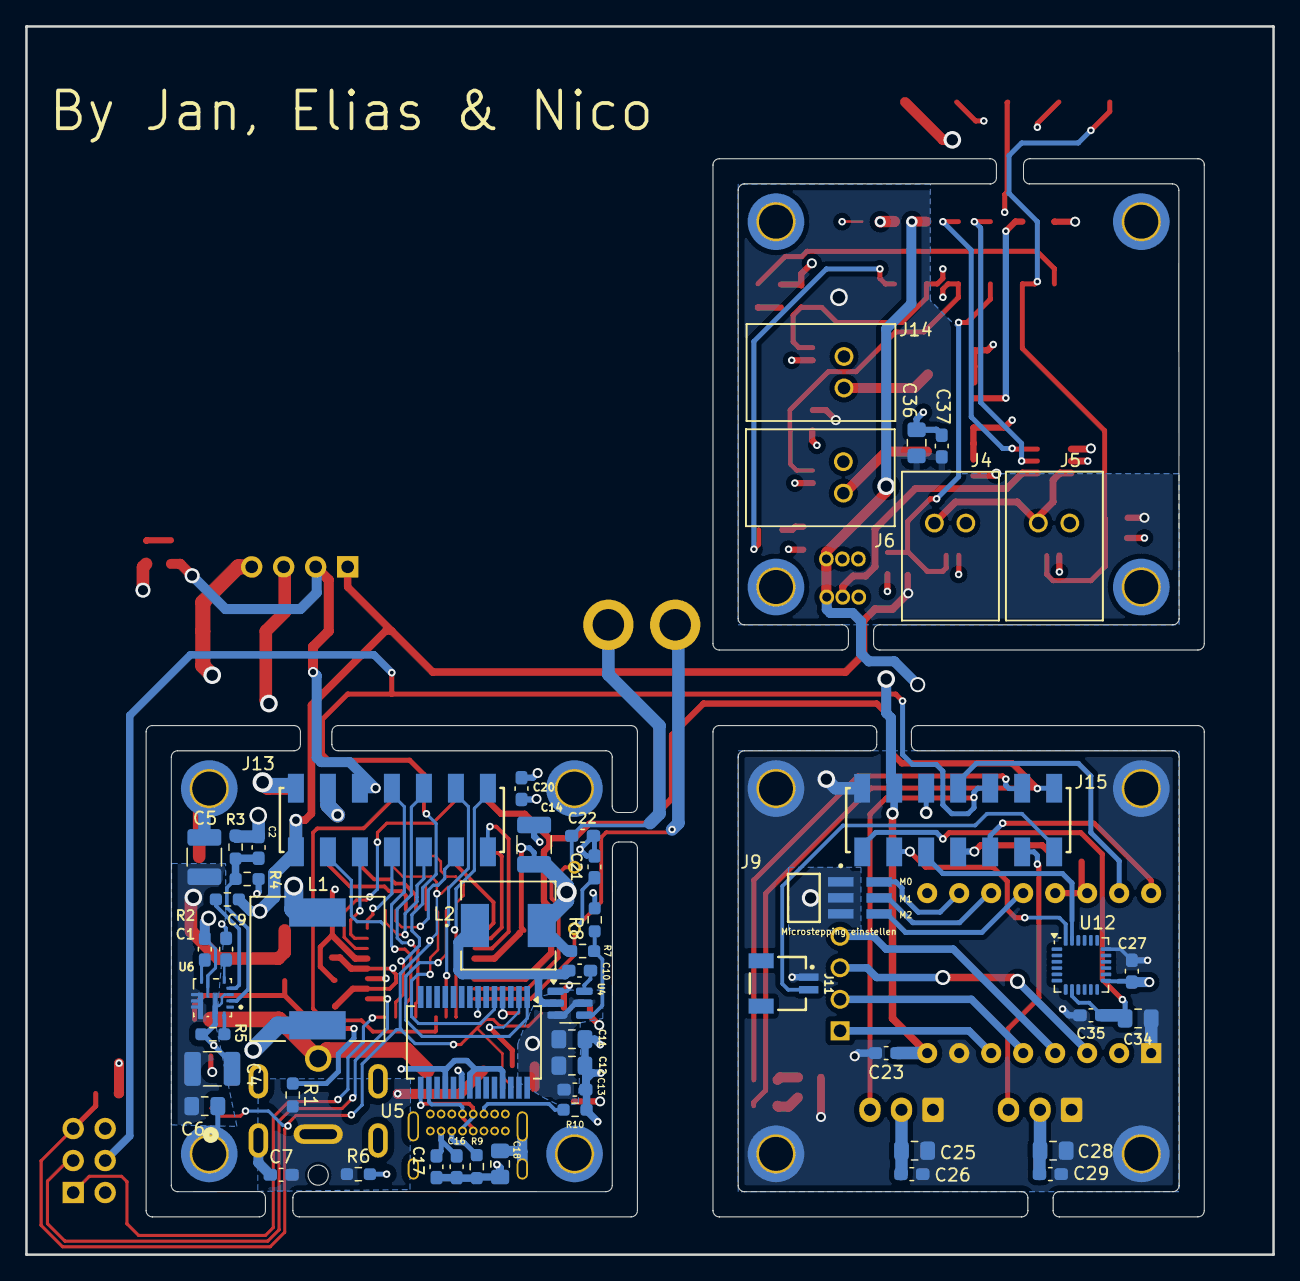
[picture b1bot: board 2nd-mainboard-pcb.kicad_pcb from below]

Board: 4 copper layers, 99.0 x 97.5 mm, 130 parts (52 on the bottom side), 71 nets.

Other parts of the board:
J2, J3: Fan_12/5V_Regelung; FTS_103_01_F_S
J4: FAN0; CONN_S2B-XH-A-1LFSN_JST
J5: FAN1; CONN_S2B-XH-A-1LFSN_JST
J6: FAN2; CONN_S2B-XH-A-1LFSN_JST
J14: FAN3; CONN_S2B-XH-A-1LFSN_JST
U7: TPM16050-S6TR; TPM16050_S6TR
U8, U9: RJK0456DPB-00-J5; RJK0456DPB_00_J5

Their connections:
+5V_POW: J2.1, J3.1; also elsewhere on the board
+12V: J2.3, J3.3; also elsewhere on the board
FAN_01_PWM_clockwise: U7.6 (IN2); also elsewhere on the board
FAN_01_PWM_counterclockwise: U7.5 (IN1); also elsewhere on the board
FAN_2_PWM: U8.4 (G); also elsewhere on the board
FAN_3_PWM: U9.4 (G); also elsewhere on the board
Fan_Versorgung_01: J2.2, U7.4 (VM)
Fan_Versorgung_23: J3.2, J6.1, J14.1
GND: U7.2 (GND), U8.1 (S), U8.2, U8.3, U9.1 (S), U9.2, U9.3; also elsewhere on the board
unnamed: J4.1, J5.1, U7.3 (OUT1)
unnamed: J4.2, J5.2, U7.1 (OUT2)
unnamed: J6.2, U8.5 (D)
unnamed: J14.2, U9.5 (D)

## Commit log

2025-03-22 updated conns
2025-03-23 todos hinzugefuegt
2025-03-24 edited temps
2025-03-25 cleanup
2025-03-25 updated todos (there's surely a better way to do this...)
2025-03-30 finished pcb design on main segment
2025-03-30 sachen hinzugefuegt
2025-03-30 diplomarbeitsbesprechungabgeschlossen
2025-03-30 stacked design verbessert, power plane aufgeteilt
2025-03-30 more layout
2025-03-31 5v flaeche, aref eingestellt, jetzt on top flaechen angehen
2025-03-31 layout backup vor drehung
2025-03-31 made better connections
2025-03-31 volle zonen auf b.cu erstellt und schaltregler symbol ausgetauscht
2025-04-01 Made traces thicker
2025-04-01 motor module traced
2025-04-02 finished Fan-module tracing, now checking ground connections and integrating test-plattform
2025-04-03 finished all traces, 59 drc check errors to go
2025-05-19 last few changes
2025-05-19 final layout improvements, next one will round corners
2025-05-19 rounded corners
2025-05-20 no more errors
2025-05-20 small tweaks
2025-05-29 references ausgebessert
2025-10-16 Enhance README with project details and badges
    Added project title, description, and badges to README.
